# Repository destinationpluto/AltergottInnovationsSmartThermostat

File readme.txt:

esptool.py --before default_reset --after hard_reset --chip esp8266 --port "COM3" --baud 115200 write_flash 0x0 .pio/build/Thermostat/firmware.bin

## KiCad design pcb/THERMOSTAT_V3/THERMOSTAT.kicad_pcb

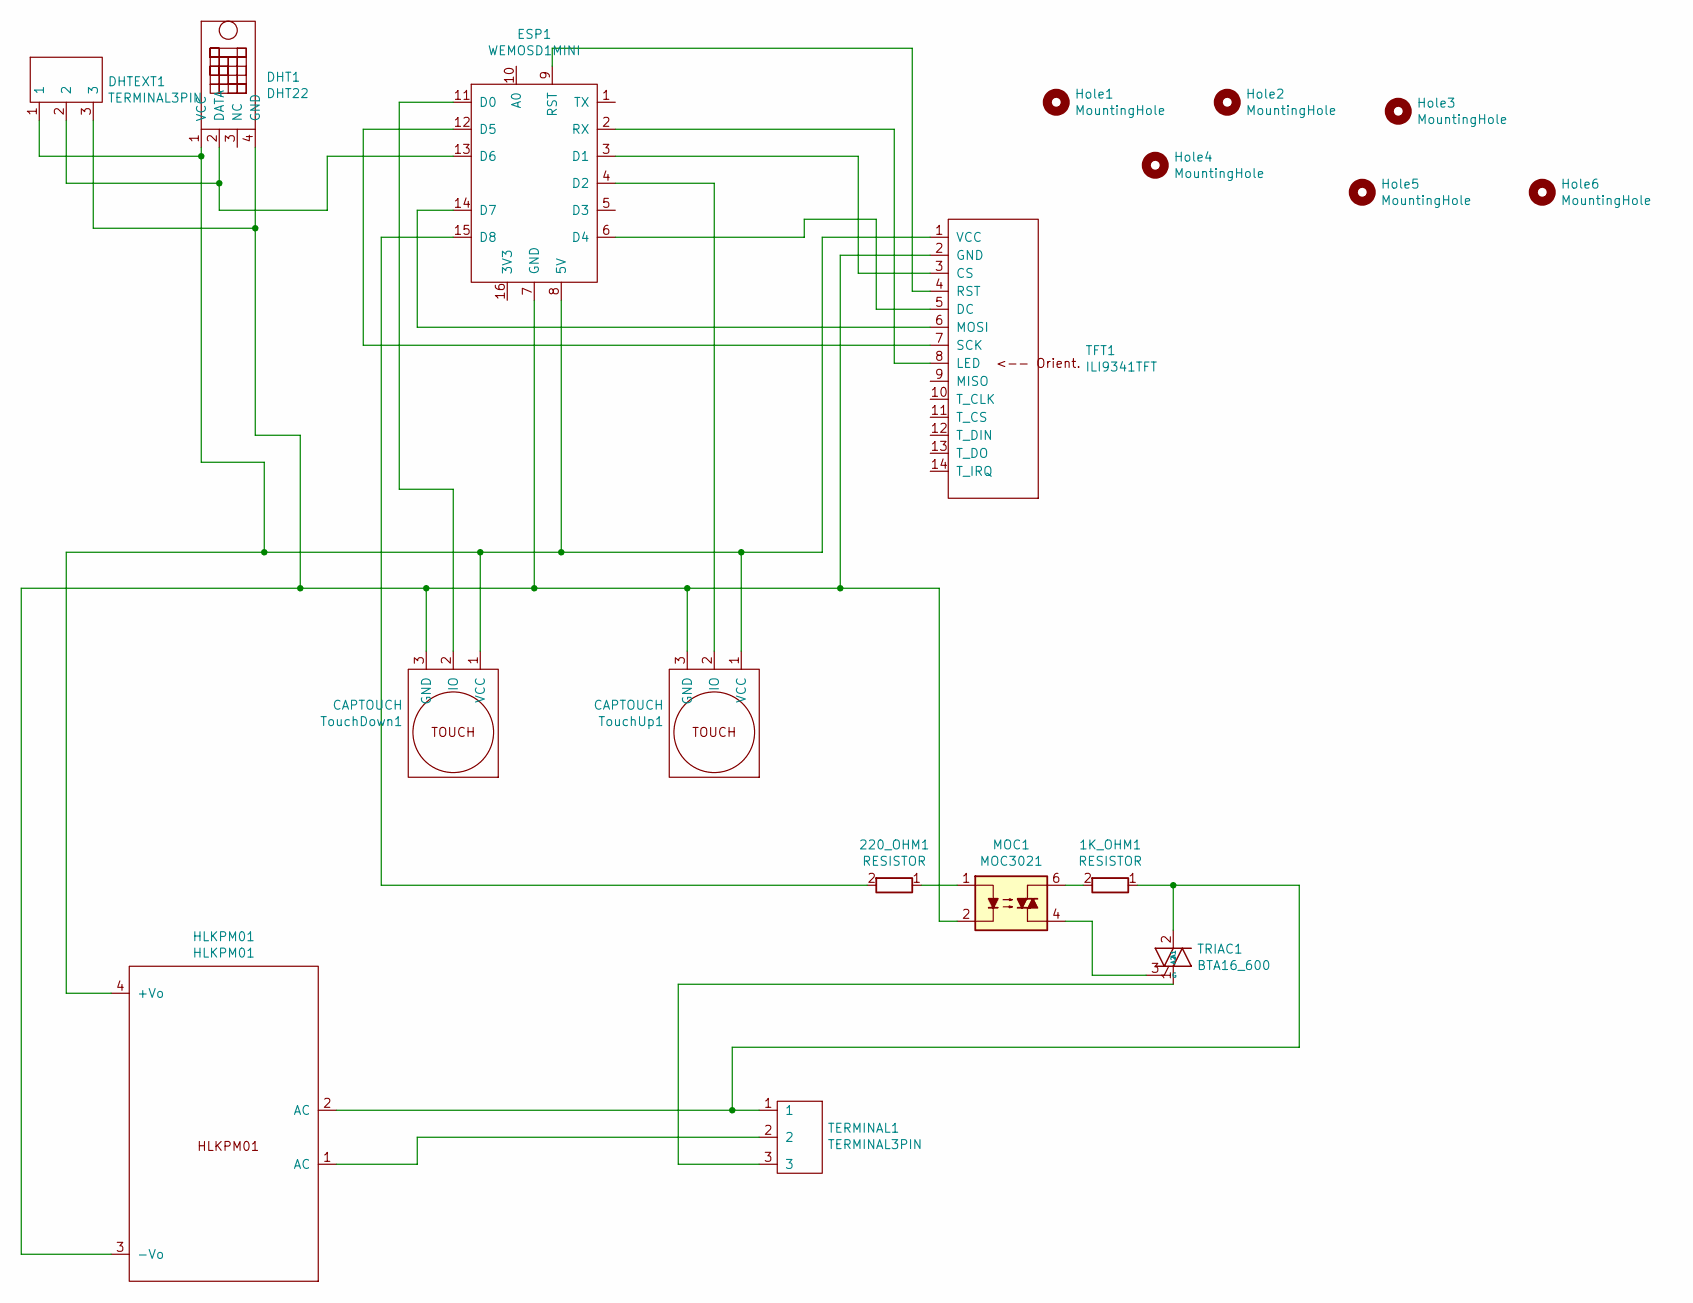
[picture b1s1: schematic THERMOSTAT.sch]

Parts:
1K_OHM1: RESISTOR; R_Axial_DIN0414_L11.9mm_D4.5mm_P15.24mm_Horizontal
220_OHM1: RESISTOR; R_Axial_DIN0207_L6.3mm_D2.5mm_P7.62mm_Horizontal
DHT1: DHT22; DHT22FOOT
DHTEXT1: TERMINAL3PIN; TERMINAL3PINFOOT
ESP1: WEMOSD1MINI; WeMosD1Mini
HLKPM01: HLKPM01; HLKPM01FOOT
Hole1, Hole2, Hole3, Hole4, Hole5, Hole6: MountingHole; MountingHole_3.2mm_M3
MOC1: MOC3021
TERMINAL1: TERMINAL3PIN; TERMINAL3PINFOOT
TFT1: ILI9341TFT; ILI9341TFTFOOT
TRIAC1: BTA16_600; BTA16FOOT
TouchDown1: CAPTOUCH; CAPTOUCHFOOT
TouchUp1: CAPTOUCH; CAPTOUCHFOOT

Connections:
unnamed: 1K_OHM1.1, HLKPM01.2 (AC), TERMINAL1.1, TRIAC1.2 (A2)
unnamed: 1K_OHM1.2, MOC1.6
unnamed: 220_OHM1.1, MOC1.1
unnamed: 220_OHM1.2, ESP1.15 (D8)
unnamed: DHT1.1 (VCC), DHTEXT1.1, ESP1.8 (5V), HLKPM01.4 (+Vo), TFT1.1 (VCC), TouchDown1.1 (VCC), TouchUp1.1 (VCC)
unnamed: DHT1.2 (DATA), DHTEXT1.2, ESP1.13 (D6)
unnamed: DHT1.4 (GND), DHTEXT1.3, ESP1.7 (GND), HLKPM01.3 (-Vo), MOC1.2, TFT1.2 (GND), TouchDown1.3 (GND), TouchUp1.3 (GND)
unnamed: ESP1.2 (RX), TFT1.8 (LED)
unnamed: ESP1.3 (D1), TFT1.3 (CS)
unnamed: ESP1.4 (D2), TouchUp1.2 (IO)
unnamed: ESP1.6 (D4), TFT1.5 (DC)
unnamed: ESP1.9 (RST), TFT1.4 (RST)
unnamed: ESP1.11 (D0), TouchDown1.2 (IO)
unnamed: ESP1.12 (D5), TFT1.7 (SCK)
unnamed: ESP1.14 (D7), TFT1.6 (MOSI)
unnamed: HLKPM01.1 (AC), TERMINAL1.2
unnamed: MOC1.4, TRIAC1.3 (G)
unnamed: TERMINAL1.3, TRIAC1.1 (A1)

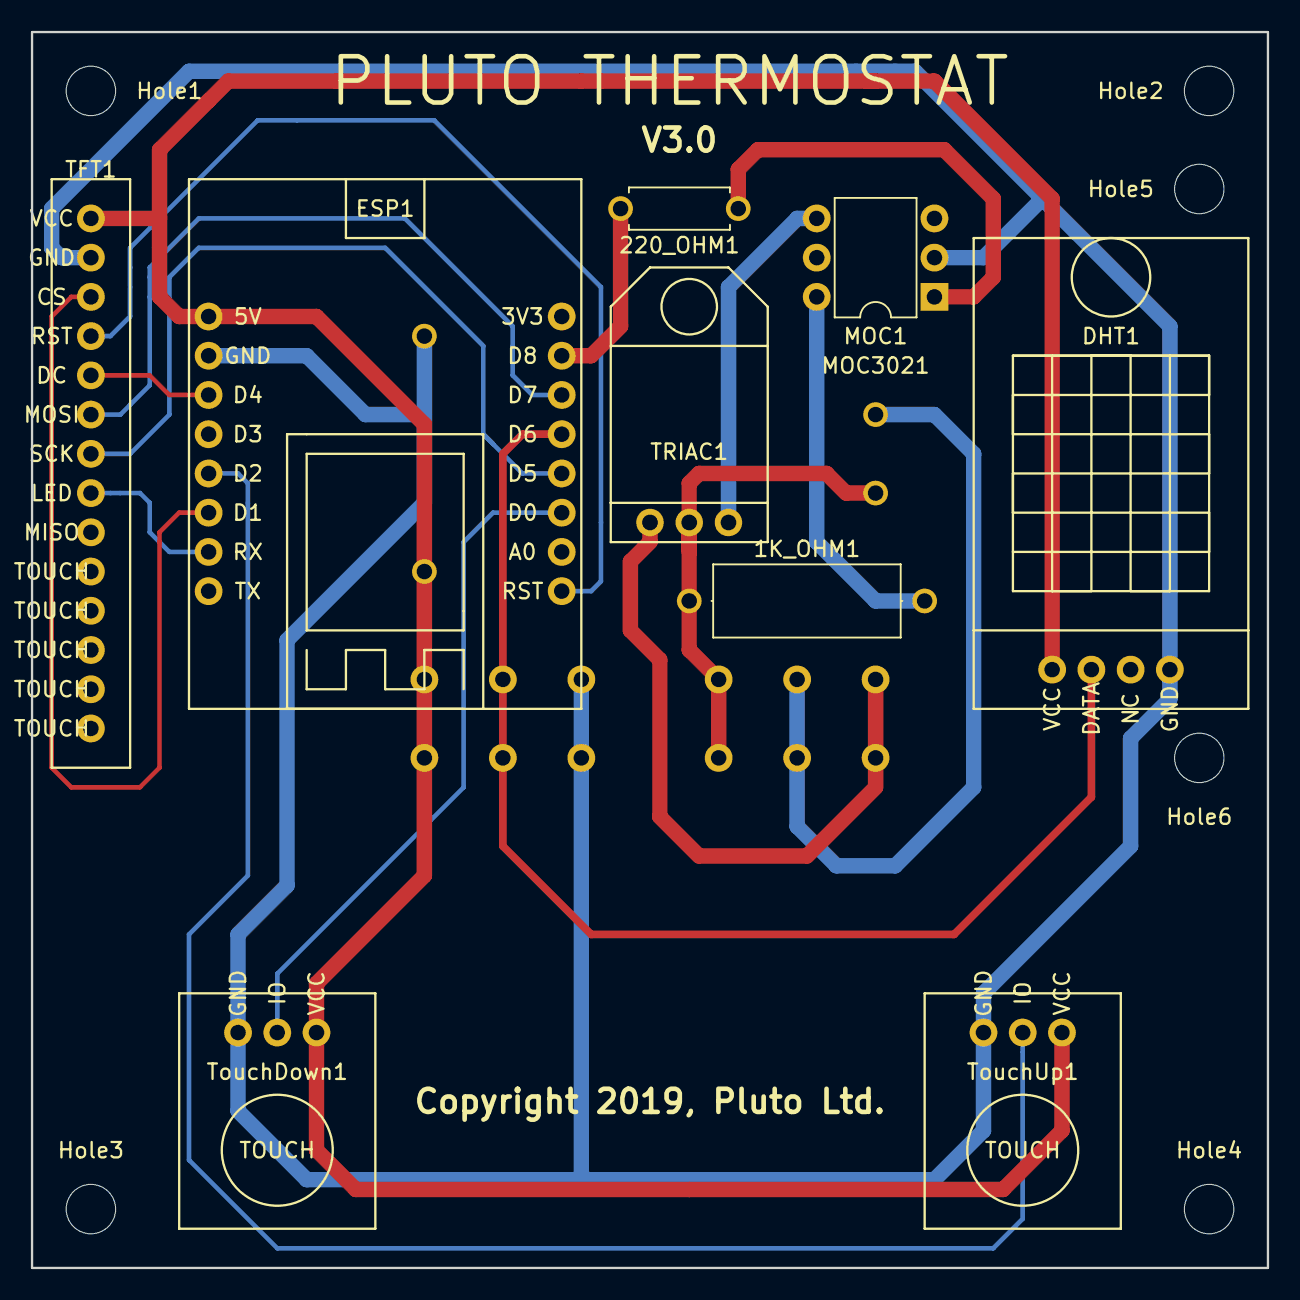
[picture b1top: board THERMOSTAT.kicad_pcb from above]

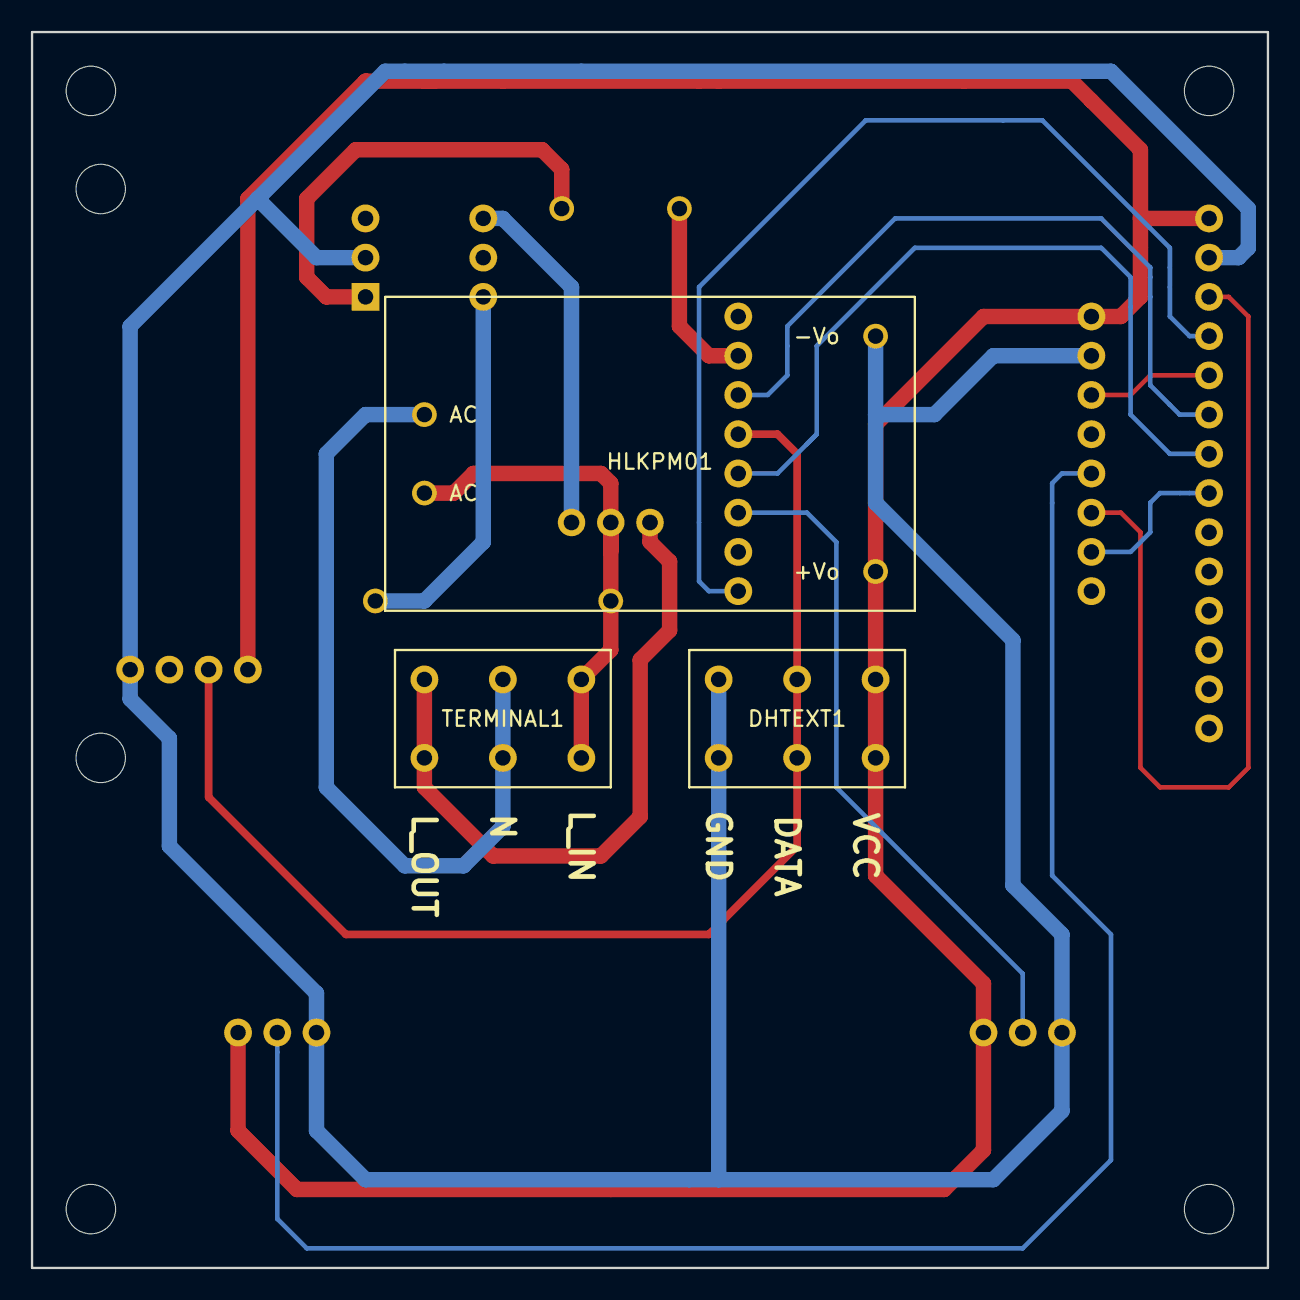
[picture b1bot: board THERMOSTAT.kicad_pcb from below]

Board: 2 copper layers, 80.0 x 80.0 mm, 18 parts (3 on the bottom side), 18 nets.

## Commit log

2023-12-26 first commit: push project to github

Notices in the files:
pcb/THERMOSTAT_V3/THERMOSTAT.kicad_pcb:
Copyright 2019, Pluto Ltd.
